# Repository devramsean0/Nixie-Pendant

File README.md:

# Nixie-Pendant
What if, Nixie Tubes (yes, 2!) on a pendant?

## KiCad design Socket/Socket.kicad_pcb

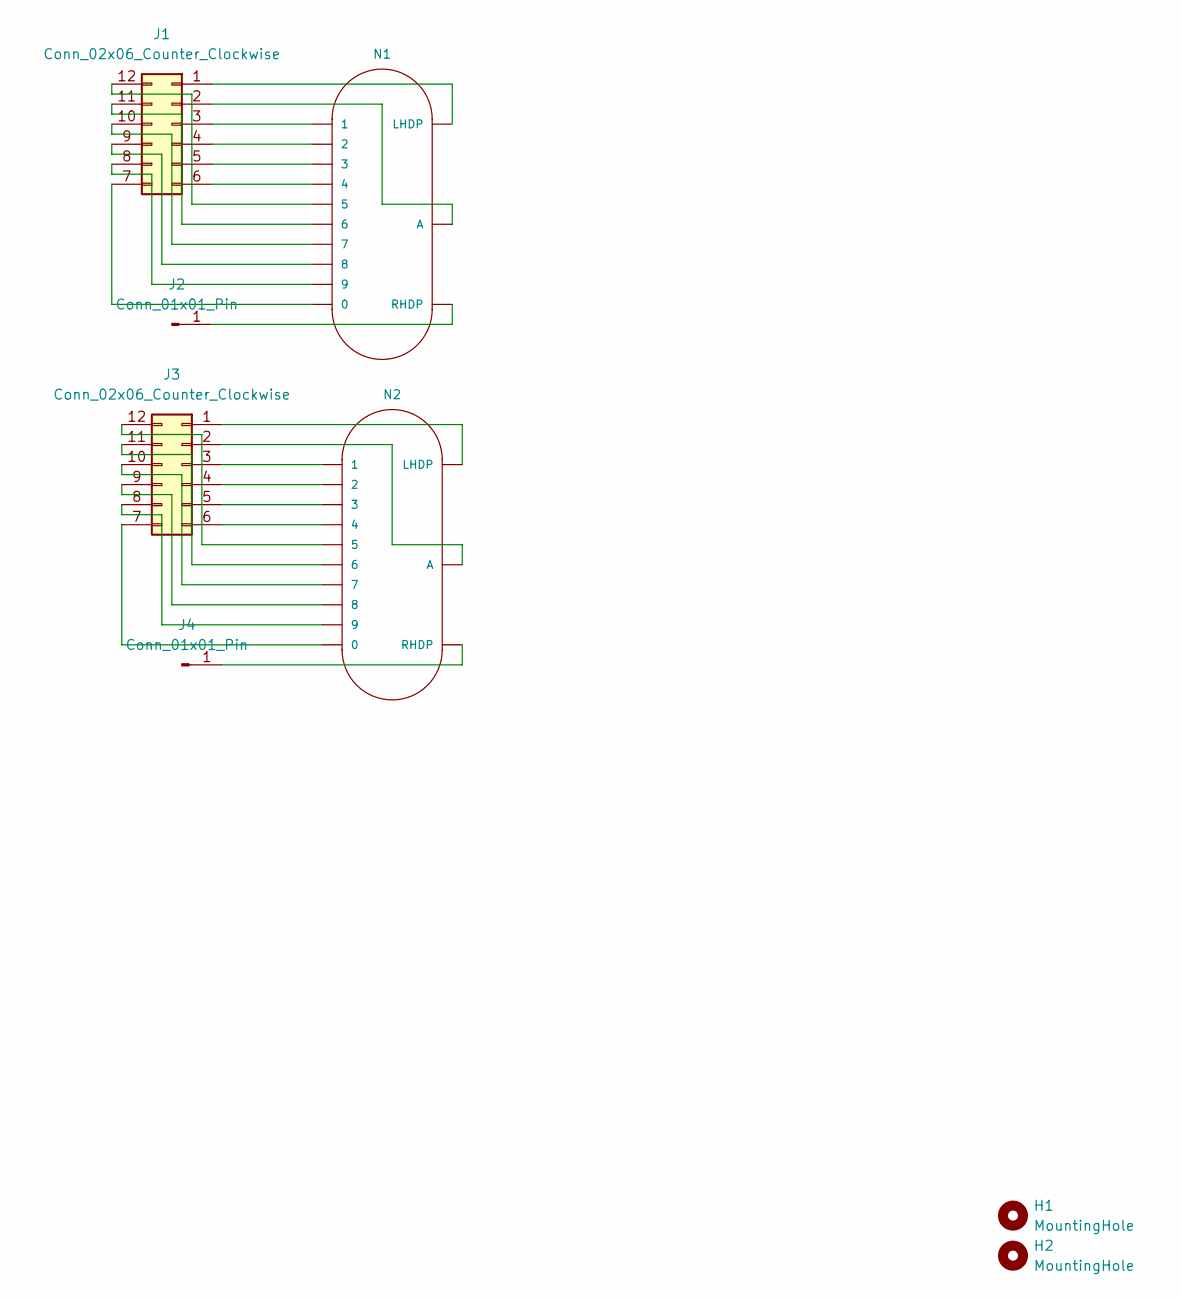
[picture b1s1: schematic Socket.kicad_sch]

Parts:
H1, H2: MountingHole; MountingHole_2.2mm_M2
J1, J3: Conn_02x06_Counter_Clockwise; PinSocket_2x06_P2.54mm_Vertical
J2, J4: Conn_01x01_Pin; PinSocket_1x01_P2.54mm_Vertical
N1, N2: IN-16; nixies-us-IN-16

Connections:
unnamed: J1.1, N1.LHDP
unnamed: J1.2, N1.A
unnamed: J1.3, N1.1
unnamed: J1.4, N1.2
unnamed: J1.5, N1.3
unnamed: J1.6, N1.4
unnamed: J1.7, N1.0
unnamed: J1.8, N1.9
unnamed: J1.9, N1.8
unnamed: J1.10, N1.7
unnamed: J1.11, N1.6
unnamed: J1.12, N1.5
unnamed: J2.1, N1.RHDP
unnamed: J3.1, N2.LHDP
unnamed: J3.2, N2.A
unnamed: J3.3, N2.1
unnamed: J3.4, N2.2
unnamed: J3.5, N2.3
unnamed: J3.6, N2.4
unnamed: J3.7, N2.0
unnamed: J3.8, N2.9
unnamed: J3.9, N2.8
unnamed: J3.10, N2.7
unnamed: J3.11, N2.6
unnamed: J3.12, N2.5
unnamed: J4.1, N2.RHDP

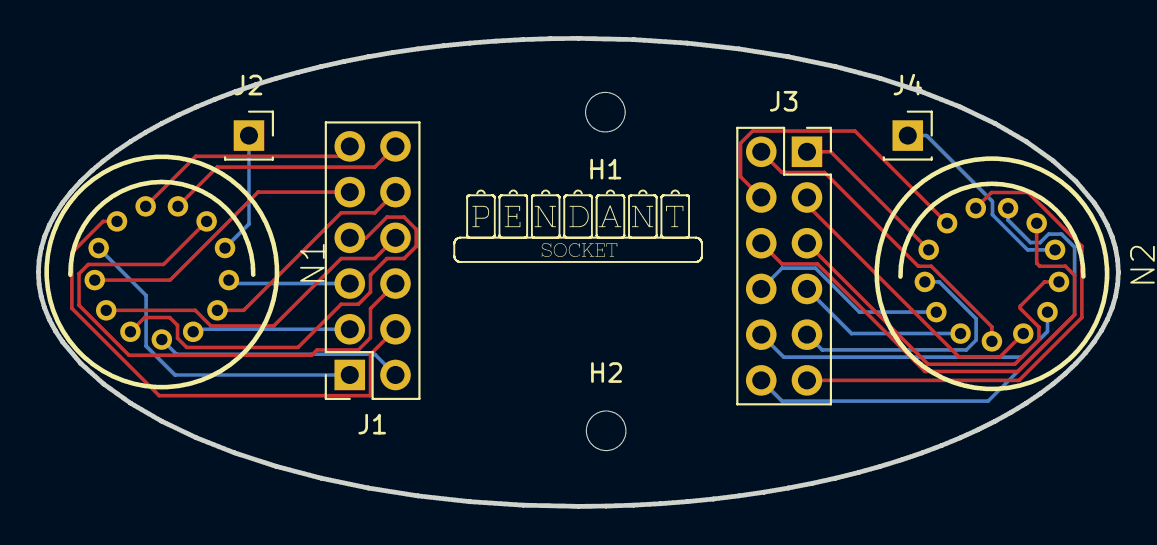
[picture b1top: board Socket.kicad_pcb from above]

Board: 2 copper layers, 60.0 x 26.0 mm, 8 parts (0 on the bottom side), 26 nets.

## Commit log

2025-05-21 Start on the Journal
2025-05-21 More thoughts
2025-05-25 Its a Socket and a Journal
2025-05-25 Low Voltage boards :yay:
